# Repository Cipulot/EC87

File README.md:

# EC87

## **DEPRECATED**

This project has been deprecated in favor of the next TKL I'm working on.
It will not be updated nor maintained from now on, so do no base projects, them being PCB or cases, on it.
The project of reference for EC TKL will be named (provisional for now, in search of a better name still): ECip TKL
This new design will join the EC60 in the reference design family of PCBs that I'm working on. Think of these as the EC equivalent of the H87/88 and H60 for MX switches. An FRL will be developed too, to complete the general layouts. Both will feature the same key and cluster spacing as the H87/88 PCBs, so that future design of cases can have both MX and EC options without compromising compatibility or having to develop separate cases/parts of cases for it.

## Introduction

EC87 is an Electrostatic Capacitive (EC) TKL keyboard PCB.

This project is a continuation of my development of open source EC boards after publishing the [Corne EC Revival](https://github.com/Cipulot/CorneECRevival).

Below is the KLE of the supported layout:

Multi layout support is planned for Rev2.

## Technical information

- Layout size: tenkeykess (TKL)
- Compatible switches: EC switches (Topre and NIZ)
- Microcontroller: STM32F411
- Connector: detachable USB Type C
- Firmware compatibility: QMK (with VIA/VIAL support)
- Protection hardware:
  - Fused
  - ESD protection

## Renders and Prototypes

### EC87 PCB

#### Render

#### Prototype

### Plate

#### Render

#### Prototype

### Backplate

#### Render

#### Prototype

## Revisions and relative features

### Rev1

First revision of the board used for validation purposes of the circuit and QMK software.

Features include:

- Extension of the analog sensing circuit used in Corne EC Revival

- STM32F411 MCU for better performance, both cycle wise and in ADC performance compared to 32U4

- APC (Actuation Point Changer) with predefined actuation points and full scale analog switch control (full board / per key)

### Rev2

Rev 2 is already in the work and will have some radical changes, to allow better compatibility, layout options and performance improvements.

Features that will be included:

- Addition of multi-layout option (ANSI, ISO and different bottom rows)

- Rework of the analog circuit, basing it off a new "standard" model that is in development by [Gondolindrim](https://github.com/Gondolindrim) (absolute chad), myself and others. This so that we achieve a reliable enough design to enable more designers and more EC boards to get into the wild.

- Dedicated PCBs for specific MX boards already being run.

## WIP

Implementation of APC and initial calibration is in development. This features will allow to choose from a set op predetermined actuation points by simply cycling through them using a key combination. The initial calibration is to ensure that the overall baseline reading is equal across all the keys. Later, in Rev2, this will be used to adjust hardware gain through dedicated control circuit.

See commits in `Firmware` for details about the state of development.

## License

<br />This work is licensed under a <a rel="license" href="http://creativecommons.org/licenses/by-nc-sa/4.0/">Creative Commons Attribution-NonCommercial-ShareAlike 4.0 International License</a>.

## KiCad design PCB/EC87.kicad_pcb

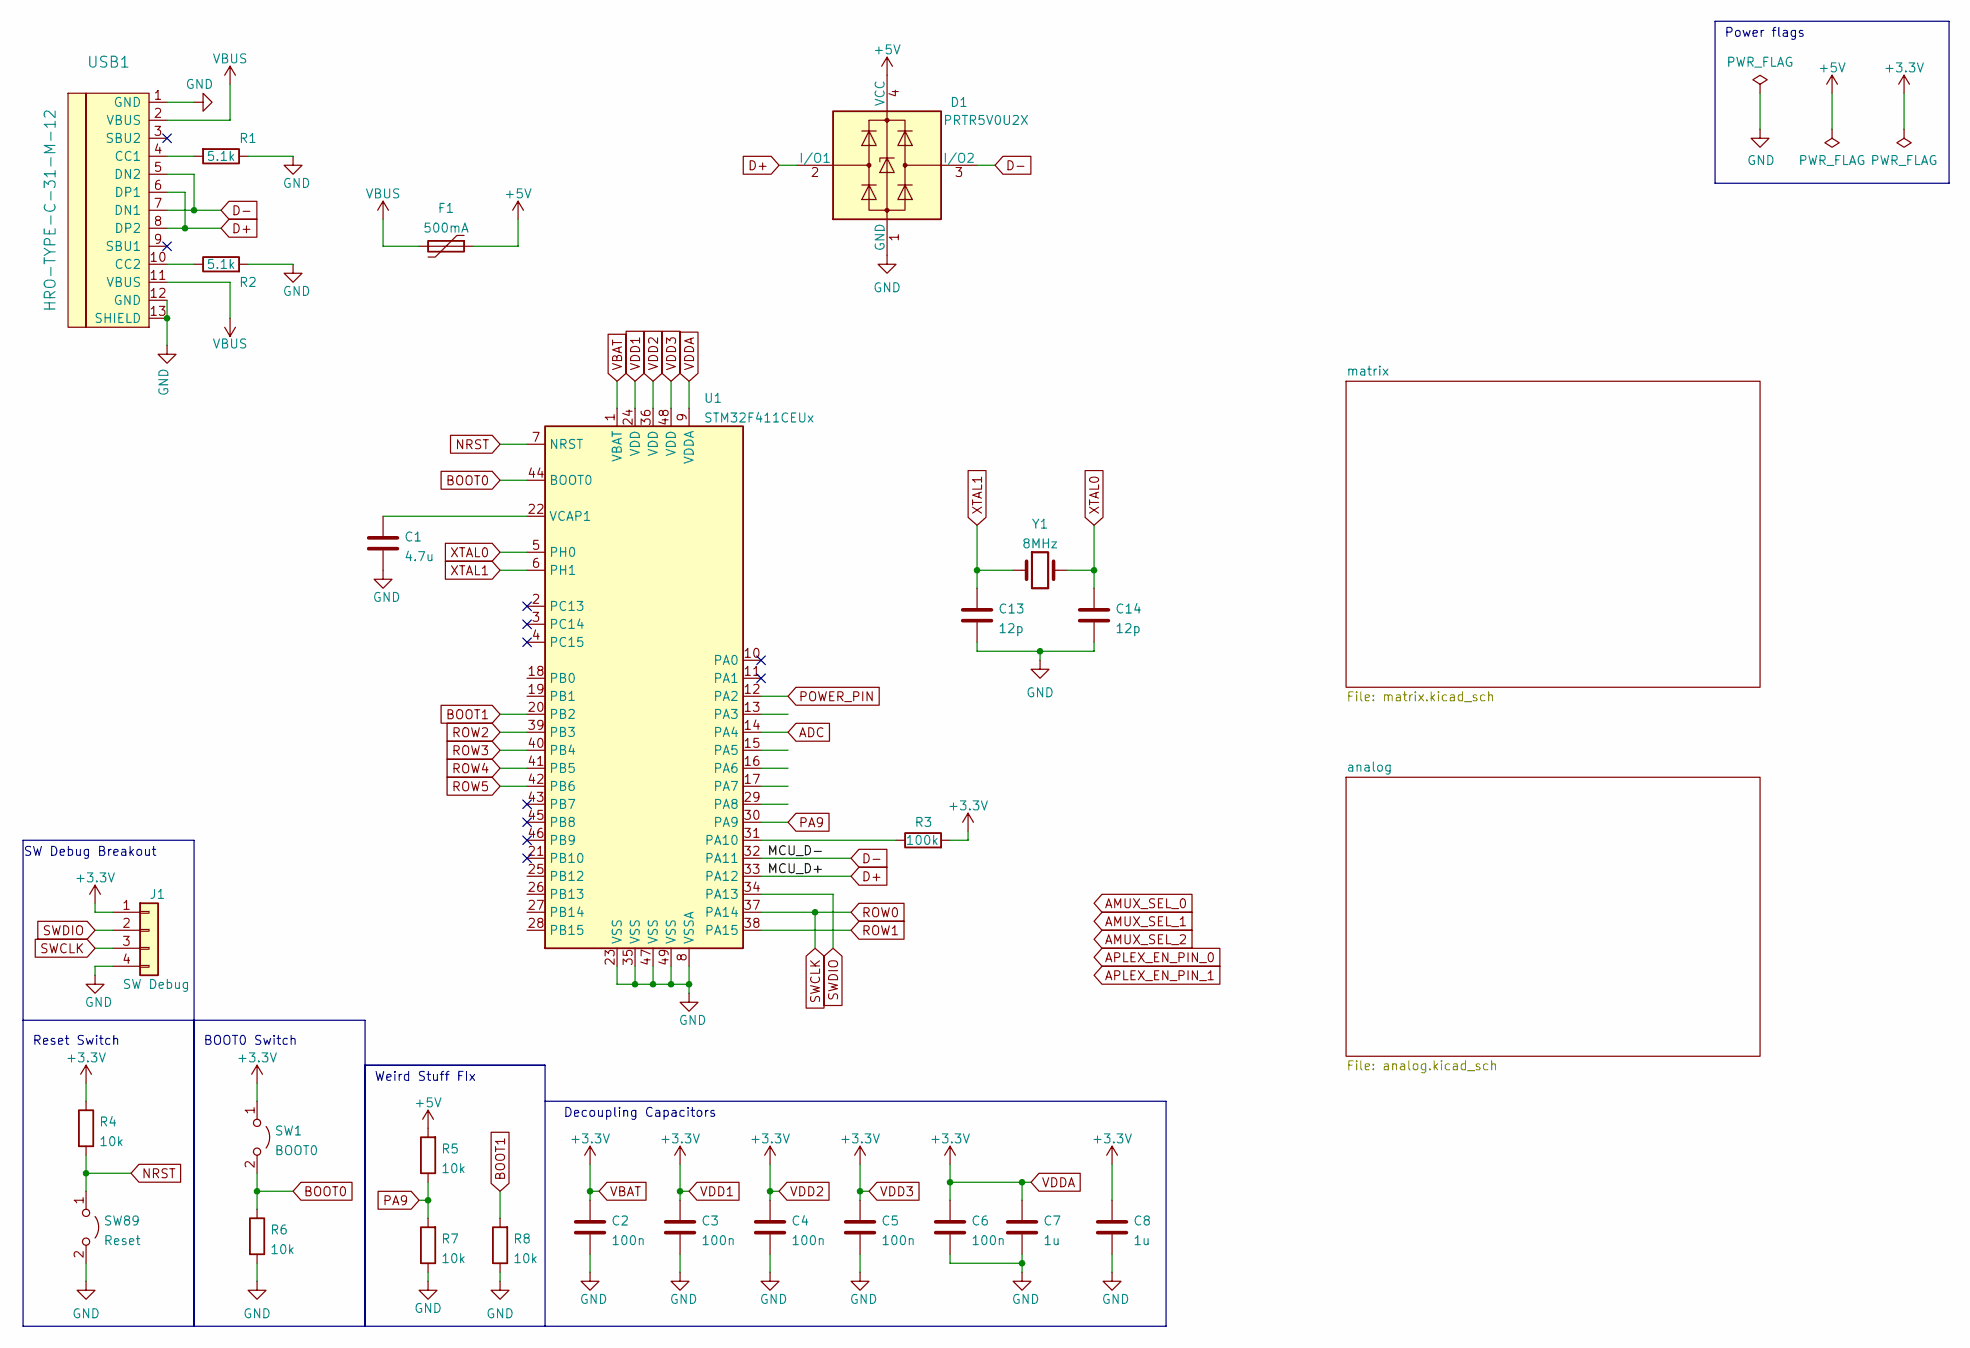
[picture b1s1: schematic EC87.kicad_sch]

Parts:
C1: 4.7u; C_0603_1608Metric
C2, C3, C4, C5, C6: 100n; C_0603_1608Metric
C7, C8: 1u; C_0603_1608Metric
C13, C14: 12p; C_0603_1608Metric
D1: PRTR5V0U2X; SOT-143
F1: 500mA; Fuse_1206_3216Metric
J1: SW Debug; PinHeader_1x04_P2.54mm_Vertical
R1, R2: 5.1k; R_0603_1608Metric
R3: 100k; R_0603_1608Metric
R4, R5, R6, R7, R8: 10k; R_0603_1608Metric
SW1: BOOT0; Jumper-UserFriendly
SW89: Reset; Jumper-UserFriendly
U1: STM32F411CEUx; QFN-48-1EP_7x7mm_P0.5mm_EP5.6x5.6mm
USB1: HRO-TYPE-C-31-M-12; HRO-TYPE-C-31-M-12-Assembly
Y1: 8MHz; Crystal_SMD_5032-2Pin_5.0x3.2mm

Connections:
+5V: D1.4 (VCC), F1.1, R5.2
ADC: U1.14 (PA4); also elsewhere on the board
BOOT0: R6.1, SW1.2 (B), U1.44 (BOOT0)
BOOT1: R8.2, U1.20 (PB2)
D+: D1.2 (I/O1), U1.33 (PA12), USB1.6 (DP1), USB1.8 (DP2)
D-: D1.3 (I/O2), U1.32 (PA11), USB1.5 (DN2), USB1.7 (DN1)
GND: C1.2, C2.2, C3.2, C4.2, C5.2, C6.2, C7.2, C8.2, C13.2, C14.2, D1.1 (GND), J1.4, R1.1, R2.2, R6.2, R7.1, R8.1, SW89.2 (B), U1.8 (VSSA), U1.23 (VSS), U1.35 (VSS), U1.47 (VSS), U1.49 (VSS), USB1.1 (GND), USB1.12 (GND), USB1.13 (SHIELD); also elsewhere on the board
NRST: R4.2, SW89.1 (A), U1.7 (NRST)
unnamed: C1.1, U1.22 (VCAP1)
unnamed: R1.2, USB1.4 (CC1)
unnamed: R2.1, USB1.10 (CC2)
unnamed: R3.1, U1.31 (PA10)
PA9: R5.1, R7.2, U1.30 (PA9)
POWER_PIN: U1.12 (PA2); also elsewhere on the board
ROW1: U1.38 (PA15); also elsewhere on the board
ROW2: U1.39 (PB3); also elsewhere on the board
ROW3: U1.40 (PB4); also elsewhere on the board
ROW4: U1.41 (PB5); also elsewhere on the board
ROW5: U1.42 (PB6); also elsewhere on the board
SWCLK: J1.3, U1.37 (PA14); also elsewhere on the board
SWDIO: J1.2, U1.34 (PA13)
VBAT: C2.1, C3.1, C4.1, C5.1, C6.1, C7.1, C8.1, J1.1, R3.2, R4.1, SW1.1 (A), U1.1 (VBAT), U1.9 (VDDA), U1.24 (VDD), U1.36 (VDD), U1.48 (VDD)
VBUS: F1.2, USB1.2 (VBUS), USB1.11 (VBUS)
XTAL0: C14.1, U1.5 (PH0), Y1.2
XTAL1: C13.1, U1.6 (PH1), Y1.1

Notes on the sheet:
BOOT0 Switch
Decoupling Capacitors
Weird Stuff FIx
Reset Switch
Power flags
SW Debug Breakout

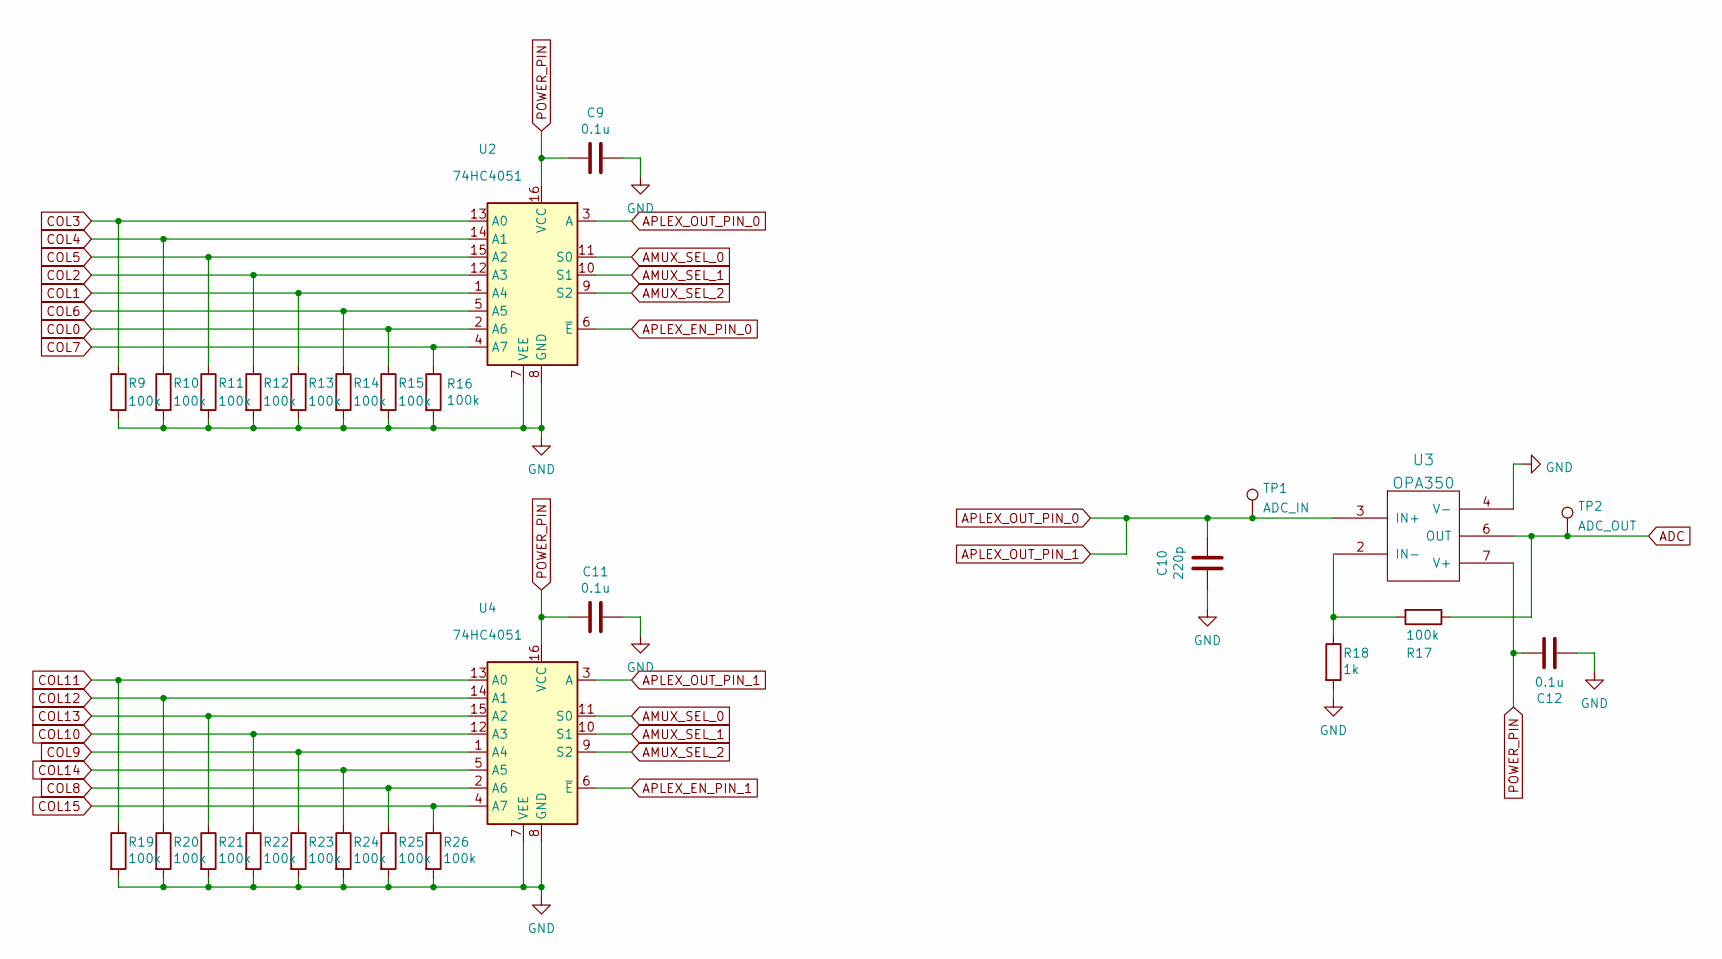
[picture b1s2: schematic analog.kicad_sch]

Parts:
C9, C11, C12: 0.1u; C_0603_1608Metric
C10: 220p; C_0603_1608Metric
R9, R10, R11, R12, R13, R14, R15, R16, R17, R19, R20, R21, R22, R23, R24, R25, R26: 100k; R_0603_1608Metric
R18: 1k; R_0603_1608Metric
TP1: ADC_IN; TestPoint_Pad_D1.0mm
TP2: ADC_OUT; TestPoint_Pad_D1.0mm
U2, U4: 74HC4051; TSSOP16
U3: OPA350; SOIC-8_3.9x4.9mm_P1.27mm

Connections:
ADC: R17.1, TP2.1, U3.6 (OUT); also elsewhere on the board
AMUX_SEL_0: U2.11 (S0), U4.11 (S0)
AMUX_SEL_1: U2.10 (S1), U4.10 (S1)
AMUX_SEL_2: U2.9 (S2), U4.9 (S2)
APLEX_EN_PIN_0: U2.6 (~E)
APLEX_EN_PIN_1: U4.6 (~E)
APLEX_OUT_PIN_0: C10.1, TP1.1, U2.3 (A), U3.3 (IN+), U4.3 (A)
COL0: R15.1, U2.2 (A6); also elsewhere on the board
COL1: R13.1, U2.1 (A4); also elsewhere on the board
COL2: R12.1, U2.12 (A3); also elsewhere on the board
COL3: R9.1, U2.13 (A0); also elsewhere on the board
COL4: R10.1, U2.14 (A1); also elsewhere on the board
COL5: R11.1, U2.15 (A2); also elsewhere on the board
COL6: R14.1, U2.5 (A5); also elsewhere on the board
COL7: R16.1, U2.4 (A7); also elsewhere on the board
COL8: R25.1, U4.2 (A6); also elsewhere on the board
COL9: R23.1, U4.1 (A4); also elsewhere on the board
COL10: R22.1, U4.12 (A3); also elsewhere on the board
COL11: R19.1, U4.13 (A0); also elsewhere on the board
COL12: R20.1, U4.14 (A1); also elsewhere on the board
COL13: R21.1, U4.15 (A2); also elsewhere on the board
COL14: R24.1, U4.5 (A5); also elsewhere on the board
COL15: R26.1, U4.4 (A7); also elsewhere on the board
GND: C9.1, C10.2, C11.1, C12.1, R9.2, R10.2, R11.2, R12.2, R13.2, R14.2, R15.2, R16.2, R18.2, R19.2, R20.2, R21.2, R22.2, R23.2, R24.2, R25.2, R26.2, U2.7 (VEE), U2.8 (GND), U3.4 (V-), U4.7 (VEE), U4.8 (GND); also elsewhere on the board
unnamed: R17.2, R18.1, U3.2 (IN-)
POWER_PIN: C9.2, C11.2, C12.2, U2.16 (VCC), U3.7 (V+), U4.16 (VCC); also elsewhere on the board

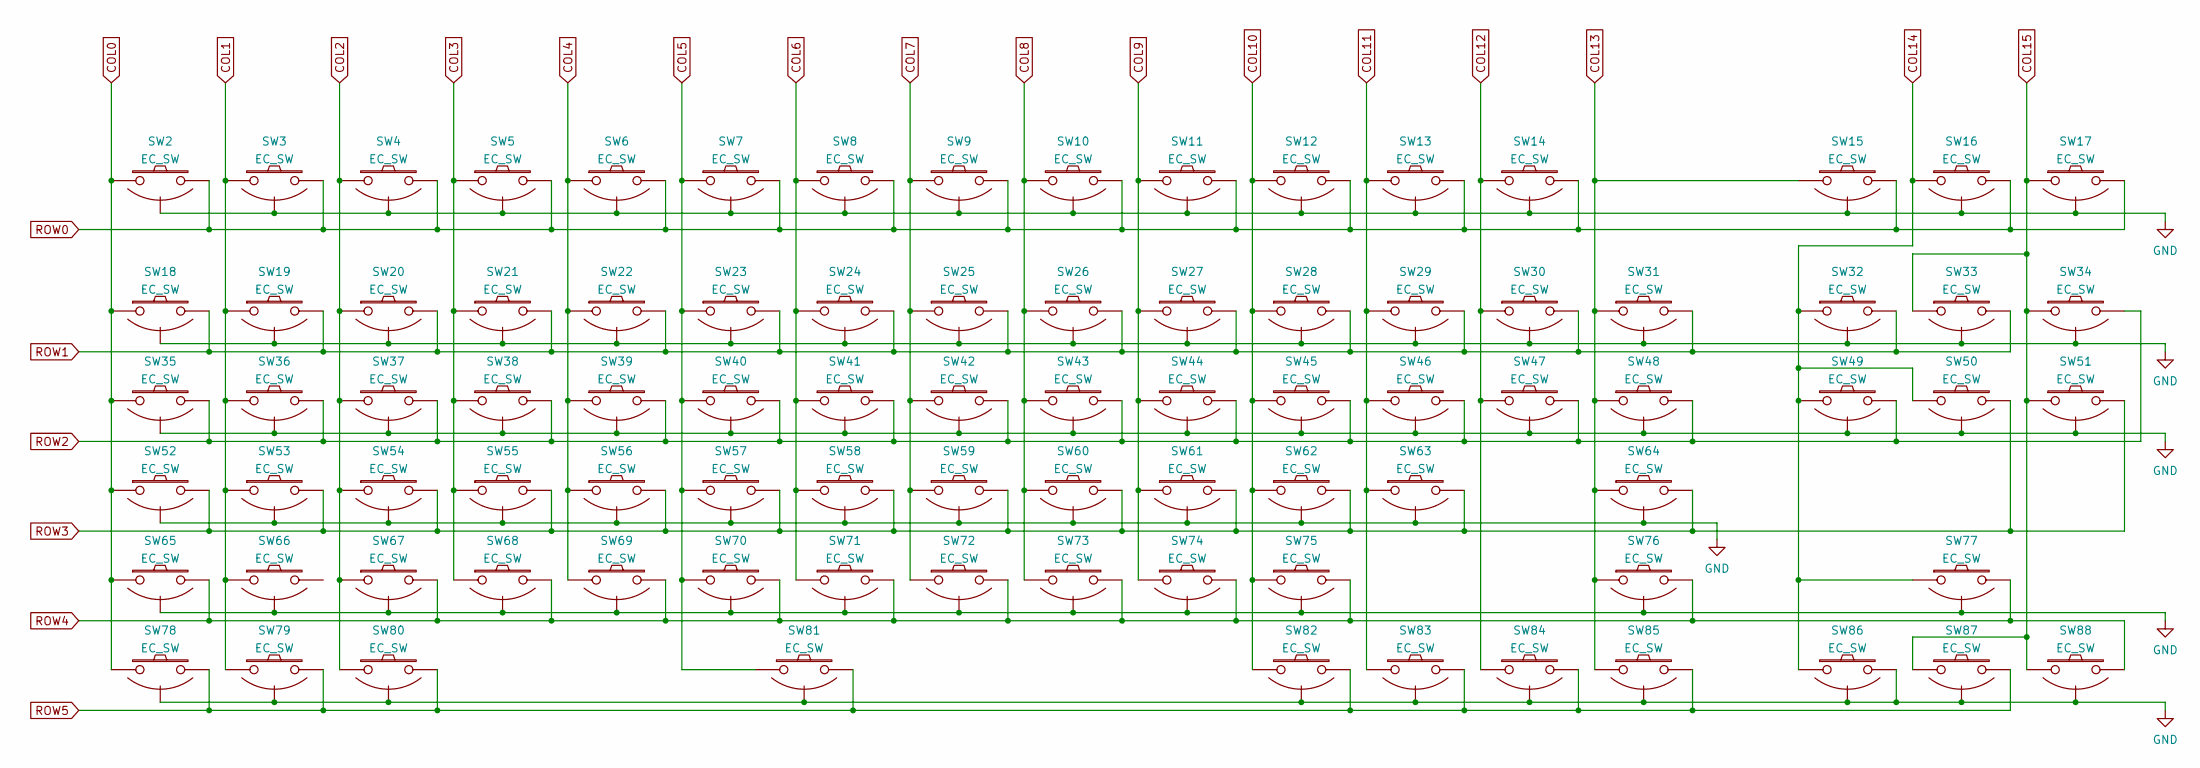
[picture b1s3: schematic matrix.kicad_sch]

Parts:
SW2, SW3, SW4, SW5, SW6, SW7, SW8, SW9, SW10, SW11, SW12, SW13, SW14, SW15, SW16, SW17, SW18, SW19, SW20, SW21, SW22, SW23, SW24, SW25, SW26, SW27, SW28, SW29, SW30, SW31, SW32, SW33, SW34, SW35, SW36, SW37, SW38, SW39, SW40, SW41, SW42, SW43, SW44, SW45, SW46, SW47, SW48, SW49, SW50, SW51, SW52, SW53, SW54, SW55, SW56, SW57, SW58, SW59, SW60, SW61, SW62, SW63, SW64, SW65, SW66, SW67, SW68, SW69, SW70, SW71, SW72, SW73, SW74, SW75, SW76, SW77, SW78, SW79, SW80, SW81, SW82, SW83, SW84, SW85, SW86, SW87, SW88: EC_SW; ecs_pad

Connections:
COL0: SW2.1, SW18.1, SW35.1, SW52.1, SW65.1, SW78.1; also elsewhere on the board
COL1: SW3.1, SW19.1, SW36.1, SW53.1, SW66.1, SW79.1; also elsewhere on the board
COL2: SW4.1, SW20.1, SW37.1, SW54.1, SW67.1, SW80.1; also elsewhere on the board
COL3: SW5.1, SW21.1, SW38.1, SW55.1, SW68.1; also elsewhere on the board
COL4: SW6.1, SW22.1, SW39.1, SW56.1, SW69.1; also elsewhere on the board
COL5: SW7.1, SW23.1, SW40.1, SW57.1, SW70.1, SW81.1; also elsewhere on the board
COL6: SW8.1, SW24.1, SW41.1, SW58.1, SW71.1; also elsewhere on the board
COL7: SW9.1, SW25.1, SW42.1, SW59.1, SW72.1; also elsewhere on the board
COL8: SW10.1, SW26.1, SW43.1, SW60.1, SW73.1; also elsewhere on the board
COL9: SW11.1, SW27.1, SW44.1, SW61.1, SW74.1; also elsewhere on the board
COL10: SW12.1, SW28.1, SW45.1, SW62.1, SW75.1, SW82.1; also elsewhere on the board
COL11: SW13.1, SW29.1, SW46.1, SW63.1, SW83.1; also elsewhere on the board
COL12: SW14.1, SW30.1, SW47.1, SW84.1; also elsewhere on the board
COL13: SW15.1, SW31.1, SW48.1, SW64.1, SW76.1, SW85.1; also elsewhere on the board
COL14: SW16.1, SW32.1, SW49.1, SW50.1, SW77.1, SW86.1; also elsewhere on the board
COL15: SW17.1, SW33.1, SW34.1, SW51.1, SW87.1, SW88.1; also elsewhere on the board
GND: SW2.3 (SG), SW3.3 (SG), SW4.3 (SG), SW5.3 (SG), SW6.3 (SG), SW7.3 (SG), SW8.3 (SG), SW9.3 (SG), SW10.3 (SG), SW11.3 (SG), SW12.3 (SG), SW13.3 (SG), SW14.3 (SG), SW15.3 (SG), SW16.3 (SG), SW17.3 (SG), SW18.3 (SG), SW19.3 (SG), SW20.3 (SG), SW21.3 (SG), SW22.3 (SG), SW23.3 (SG), SW24.3 (SG), SW25.3 (SG), SW26.3 (SG), SW27.3 (SG), SW28.3 (SG), SW29.3 (SG), SW30.3 (SG), SW31.3 (SG), SW32.3 (SG), SW33.3 (SG), SW34.3 (SG), SW35.3 (SG), SW36.3 (SG), SW37.3 (SG), SW38.3 (SG), SW39.3 (SG), SW40.3 (SG), SW41.3 (SG), SW42.3 (SG), SW43.3 (SG), SW44.3 (SG), SW45.3 (SG), SW46.3 (SG), SW47.3 (SG), SW48.3 (SG), SW49.3 (SG), SW50.3 (SG), SW51.3 (SG), SW52.3 (SG), SW53.3 (SG), SW54.3 (SG), SW55.3 (SG), SW56.3 (SG), SW57.3 (SG), SW58.3 (SG), SW59.3 (SG), SW60.3 (SG), SW61.3 (SG), SW62.3 (SG), SW63.3 (SG), SW64.3 (SG), SW65.3 (SG), SW66.3 (SG), SW67.3 (SG), SW68.3 (SG), SW69.3 (SG), SW70.3 (SG), SW71.3 (SG), SW72.3 (SG), SW73.3 (SG), SW74.3 (SG), SW75.3 (SG), SW76.3 (SG), SW77.3 (SG), SW78.3 (SG), SW79.3 (SG), SW80.3 (SG), SW81.3 (SG), SW82.3 (SG), SW83.3 (SG), SW84.3 (SG), SW85.3 (SG), SW86.2, SW86.3 (SG), SW87.3 (SG), SW88.3 (SG); also elsewhere on the board
ROW1: SW18.2, SW19.2, SW20.2, SW21.2, SW22.2, SW23.2, SW24.2, SW25.2, SW26.2, SW27.2, SW28.2, SW29.2, SW30.2, SW31.2, SW32.2, SW33.2; also elsewhere on the board
ROW2: SW34.2, SW35.2, SW36.2, SW37.2, SW38.2, SW39.2, SW40.2, SW41.2, SW42.2, SW43.2, SW44.2, SW45.2, SW46.2, SW47.2, SW48.2, SW49.2; also elsewhere on the board
ROW3: SW50.2, SW51.2, SW52.2, SW53.2, SW54.2, SW55.2, SW56.2, SW57.2, SW58.2, SW59.2, SW60.2, SW61.2, SW62.2, SW63.2, SW64.2; also elsewhere on the board
ROW4: SW65.2, SW67.2, SW68.2, SW69.2, SW70.2, SW71.2, SW72.2, SW73.2, SW74.2, SW75.2, SW76.2, SW77.2, SW88.2; also elsewhere on the board
ROW5: SW78.2, SW79.2, SW80.2, SW81.2, SW82.2, SW83.2, SW84.2, SW85.2, SW87.2; also elsewhere on the board
SWCLK: SW2.2, SW3.2, SW4.2, SW5.2, SW6.2, SW7.2, SW8.2, SW9.2, SW10.2, SW11.2, SW12.2, SW13.2, SW14.2, SW15.2, SW16.2, SW17.2; also elsewhere on the board

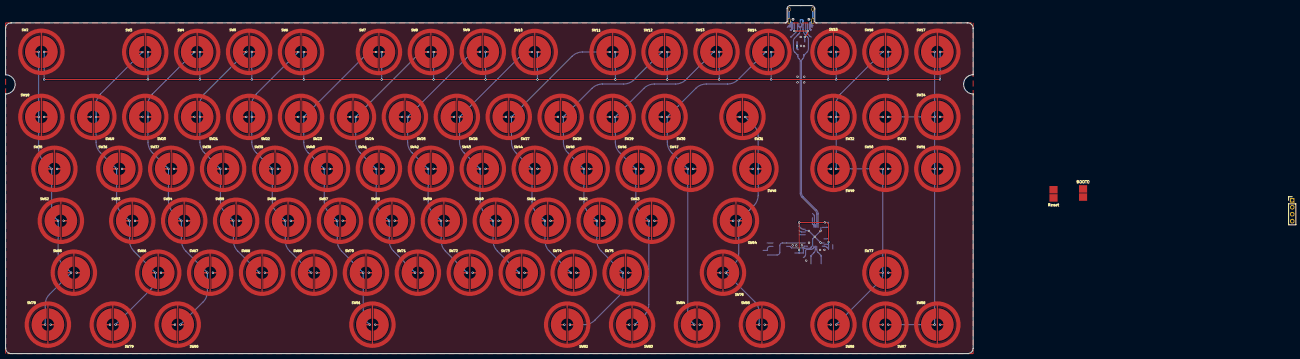
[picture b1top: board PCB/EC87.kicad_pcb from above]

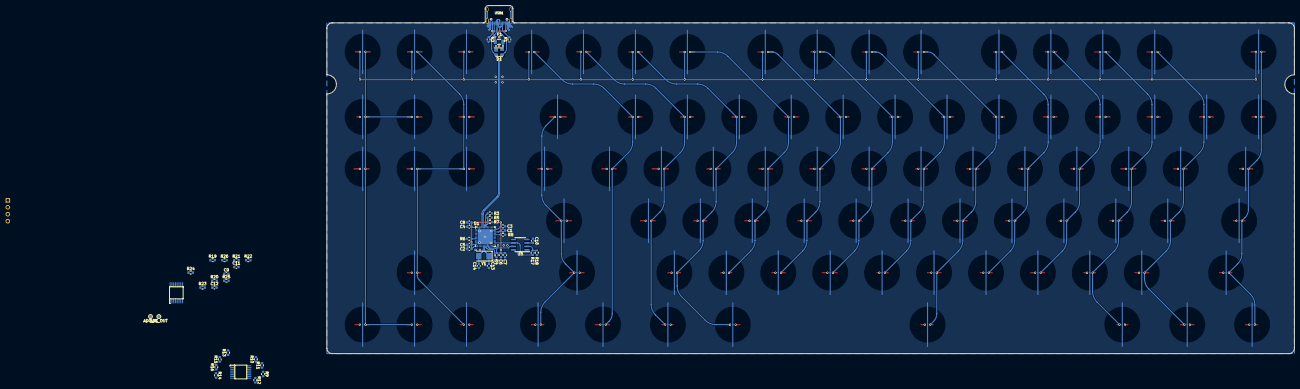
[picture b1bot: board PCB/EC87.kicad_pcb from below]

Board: 2 copper layers, 354.0 x 127.3 mm, 140 parts (50 on the bottom side), 46 nets.

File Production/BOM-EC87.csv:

Comment,Designator,Footprint,LCSC
OPA350,U3,SOIC-8_3.9x4.9mm_P1.27mm,C13388
100k,R24,R_0603_1608Metric,C25803
100n,C4,C_0603_1608Metric,C14663
100k,R20,R_0603_1608Metric,C25803
100k,R3,R_0603_1608Metric,C25803
100k,R13,R_0603_1608Metric,C25803
PRTR5V0U2X,D1,SOT-143,C2827688
100k,R12,R_0603_1608Metric,C25803
100k,R11,R_0603_1608Metric,C25803
10k,R5,R_0603_1608Metric,C25804
0.1u,C9,C_0603_1608Metric,C14663
100k,R19,R_0603_1608Metric,C25803
74HC4051,U4,TSSOP16,C5645
STM32F411CEUx,U1,QFN-48-1EP_7x7mm_P0.5mm_EP5.6x5.6mm,C60420
100k,R26,R_0603_1608Metric,C25803
100k,R23,R_0603_1608Metric,C25803
100k,R21,R_0603_1608Metric,C25803
10k,R8,R_0603_1608Metric,C25804
74HC4051,U2,TSSOP16,C5645
0.1u,C12,C_0603_1608Metric,C14663
100k,R25,R_0603_1608Metric,C25803
220p,C10,C_0603_1608Metric,C302060
10k,R7,R_0603_1608Metric,C25804
0.1u,C11,C_0603_1608Metric,C14663
100k,R10,R_0603_1608Metric,C25803
100n,C6,C_0603_1608Metric,C14663
10k,R4,R_0603_1608Metric,C25804
100n,C3,C_0603_1608Metric,C14663
100k,R17,R_0603_1608Metric,C25803
500mA,F1,Fuse_1206_3216Metric,C70076
100k,R9,R_0603_1608Metric,C25803
HRO-TYPE-C-31-M-12,USB1,HRO-TYPE-C-31-M-12-Assembly,C165948
100k,R22,R_0603_1608Metric,C25803
100k,R16,R_0603_1608Metric,C25803
10k,R6,R_0603_1608Metric,C25804
100n,C5,C_0603_1608Metric,C14663
5.1k,R1,R_0603_1608Metric,C23186
100k,R15,R_0603_1608Metric,C25803
1k,R18,R_0603_1608Metric,C21190
100k,R14,R_0603_1608Metric,C25803
5.1k,R2,R_0603_1608Metric,C23186
4.7u,C1,C_0603_1608Metric,C19666
100n,C2,C_0603_1608Metric,C14663
1u,C8,C_0603_1608Metric,C15849
1u,C7,C_0603_1608Metric,C15849

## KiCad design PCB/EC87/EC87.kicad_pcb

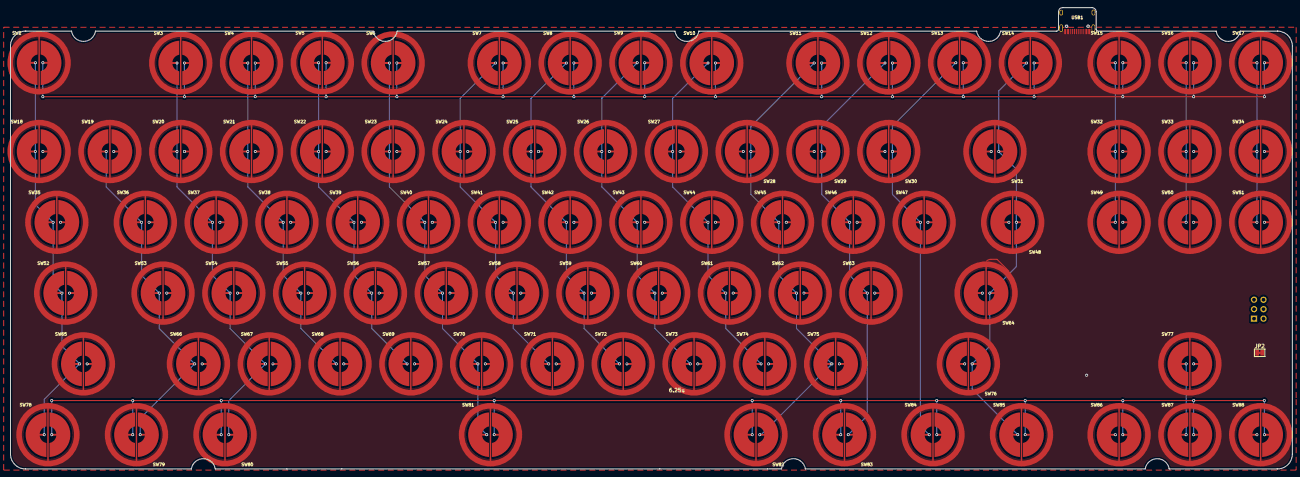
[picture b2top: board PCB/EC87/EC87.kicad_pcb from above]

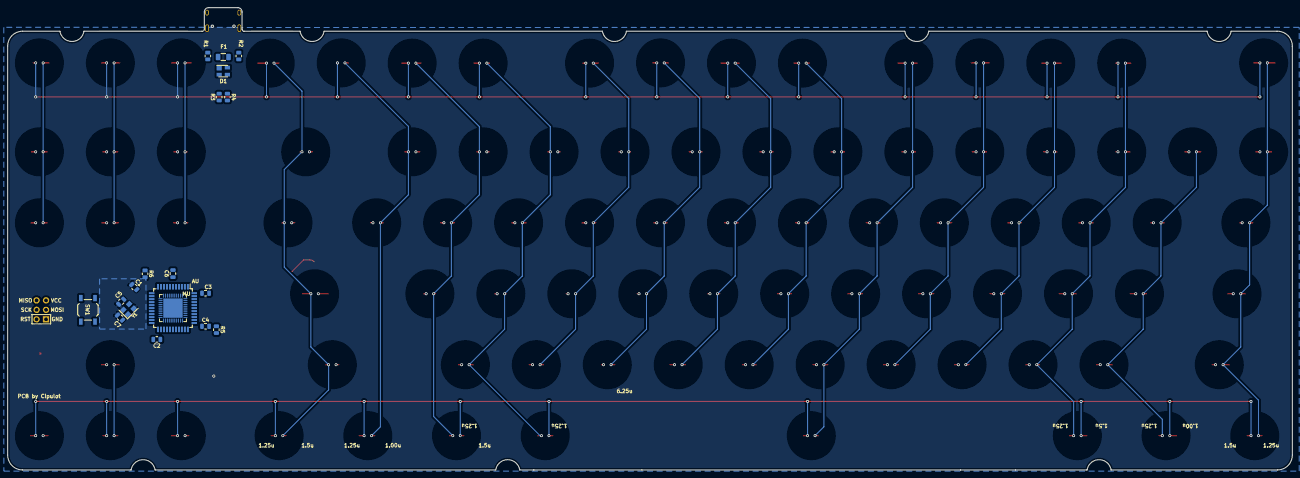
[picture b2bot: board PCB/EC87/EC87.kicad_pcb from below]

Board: 2 copper layers, 344.0 x 123.8 mm, 109 parts (20 on the bottom side), 46 nets.

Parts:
AU: ATmega32U4-A; TQFP-44_10x10mm_P0.8mm
C1, C2, C3: 0.1u; C_0805_2012Metric
C4: 10u; C_0805_2012Metric
C5, C7: 22p; C_0805_2012Metric
C6: 1u; C_0805_2012Metric
D1: PRTR5V0U2X; SOT-143
F1: 500mA; Fuse_1206_3216Metric
J1: AVR-ISP-6-Connector; Reset_Pretty
JP2: Jumper_NC_Small; SolderJumper-2_P1.3mm_Bridged_Pad1.0x1.5mm
MU: QFN-44-1EP_7x7mm_P0.5mm_EP5.2x5.2mm
R1, R2: 5.1k; R_0805_2012Metric
R3, R4: 22; R_0805_2012Metric
R5, R6: 10k; R_0805_2012Metric
SW1: SW_Push; SW_SPST_TL3342
SW2, SW3, SW4, SW5, SW6, SW7, SW8, SW9, SW10, SW11, SW12, SW13, SW14, SW15, SW16, SW17, SW18, SW19, SW20, SW21, SW22, SW23, SW24, SW25, SW26, SW27, SW28, SW29, SW30, SW31, SW32, SW33, SW34, SW35, SW36, SW37, SW38, SW39, SW40, SW41, SW42, SW43, SW44, SW45, SW46, SW47, SW48, SW49, SW50, SW51, SW52, SW53, SW54, SW55, SW56, SW57, SW58, SW59, SW60, SW61, SW62, SW63, SW64, SW65, SW66, SW67, SW68, SW69, SW70, SW71, SW72, SW73, SW74, SW75, SW76, SW77, SW78, SW79, SW80, SW81, SW82, SW83, SW84, SW85, SW86, SW87, SW88: EC_SW; ecs_pad
USB1: HRO-TYPE-C-31-M-12; HRO-TYPE-C-31-M-12-Assembly
Y1: 16MHz; Crystal_SMD_3225-4pin_3.2x2.5mm

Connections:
/MCU_D+: AU.4 (D+), MU.4, R3.2
/MCU_D-: AU.3 (D-), MU.3, R4.2
COL0: AU.41 (PF0), MU.41, SW2.1, SW18.1, SW35.1, SW52.1, SW65.1, SW78.1
COL1: AU.40 (PF1), MU.40, SW19.1, SW36.1, SW53.1, SW66.1, SW79.1
COL2: AU.39 (PF4), MU.39, SW3.1, SW20.1, SW37.1, SW54.1, SW67.1, SW80.1
COL3: AU.38 (PF5), MU.38, SW4.1, SW21.1, SW38.1, SW55.1, SW68.1
COL4: AU.37 (PF6), MU.37, SW5.1, SW22.1, SW39.1, SW56.1, SW69.1
COL5: AU.36 (PF7), MU.36, SW6.1, SW23.1, SW40.1, SW57.1, SW70.1, SW81.1
COL6: AU.32 (PC7), MU.32, SW7.1, SW24.1, SW41.1, SW58.1, SW71.1
COL7: AU.31 (PC6), MU.31, SW8.1, SW25.1, SW42.1, SW59.1, SW72.1
COL8: AU.20 (PD2), MU.20, SW9.1, SW26.1, SW43.1, SW60.1, SW73.1
COL9: SW10.1, SW27.1, SW44.1, SW61.1, SW74.1
COL10: SW11.1, SW28.1, SW45.1, SW62.1, SW75.1, SW82.1
COL11: SW12.1, SW29.1, SW46.1, SW63.1, SW83.1
COL12: SW13.1, SW30.1, SW47.1, SW84.1
COL13: SW14.1, SW31.1, SW48.1, SW64.1, SW76.1, SW85.1
COL14: SW15.1, SW32.1, SW49.1, SW86.1
COL15: SW16.1, SW33.1, SW50.1, SW77.1, SW87.1
COL16: SW17.1, SW34.1, SW51.1, SW88.1
Caps_LED: AU.22 (PD5), MU.22
D+: D1.2 (I/O1), R3.1, USB1.6 (DP1), USB1.8 (DP2)
D-: D1.3 (I/O2), R4.1, USB1.5 (DN2), USB1.7 (DN1)
GND: AU.5 (UGND), AU.15 (GND), AU.23 (GND), AU.35 (GND), AU.43 (GND), C1.2, C2.2, C3.2, C4.2, C5.1, C6.2, C7.1, D1.1 (GND), J1.6 (GND), JP2.2, MU.5, MU.15, MU.23, MU.35, MU.43, MU.45, R1.1, R2.2, R5.2, SW1.1, USB1.1 (GND), USB1.12 (GND), USB1.13 (SHIELD), Y1.2, Y1.4
GNDA: JP2.1, SW2.3 (SG), SW3.3 (SG), SW4.3 (SG), SW5.3 (SG), SW6.3 (SG), SW7.3 (SG), SW8.3 (SG), SW9.3 (SG), SW10.3 (SG), SW11.3 (SG), SW12.3 (SG), SW13.3 (SG), SW14.3 (SG), SW15.3 (SG), SW16.3 (SG), SW17.3 (SG), SW18.3 (SG), SW19.3 (SG), SW20.3 (SG), SW21.3 (SG), SW22.3 (SG), SW23.3 (SG), SW24.3 (SG), SW25.3 (SG), SW26.3 (SG), SW27.3 (SG), SW28.3 (SG), SW29.3 (SG), SW30.3 (SG), SW31.3 (SG), SW32.3 (SG), SW33.3 (SG), SW34.3 (SG), SW35.3 (SG), SW36.3 (SG), SW37.3 (SG), SW38.3 (SG), SW39.3 (SG), SW40.3 (SG), SW41.3 (SG), SW42.3 (SG), SW43.3 (SG), SW44.3 (SG), SW45.3 (SG), SW46.3 (SG), SW47.3 (SG), SW48.3 (SG), SW49.3 (SG), SW50.3 (SG), SW51.3 (SG), SW52.3 (SG), SW53.3 (SG), SW54.3 (SG), SW55.3 (SG), SW56.3 (SG), SW57.3 (SG), SW58.3 (SG), SW59.3 (SG), SW60.3 (SG), SW61.3 (SG), SW62.3 (SG), SW63.3 (SG), SW64.3 (SG), SW65.3 (SG), SW66.3 (SG), SW67.3 (SG), SW68.3 (SG), SW69.3 (SG), SW70.3 (SG), SW71.3 (SG), SW72.3 (SG), SW73.3 (SG), SW74.3 (SG), SW75.3 (SG), SW76.3 (SG), SW77.3 (SG), SW78.3 (SG), SW79.3 (SG), SW80.3 (SG), SW81.3 (SG), SW82.3 (SG), SW83.3 (SG), SW84.3 (SG), SW85.3 (SG), SW86.3 (SG), SW87.3 (SG), SW88.3 (SG)
MISO: AU.11 (PB3), J1.1 (MISO), MU.11, SW52.2, SW53.2, SW54.2, SW55.2, SW56.2, SW57.2, SW58.2, SW59.2, SW60.2, SW61.2, SW62.2, SW63.2, SW64.2
MOSI: AU.10 (PB2), J1.4 (MOSI), MU.10, SW35.2, SW36.2, SW37.2, SW38.2, SW39.2, SW40.2, SW41.2, SW42.2, SW43.2, SW44.2, SW45.2, SW46.2, SW47.2, SW48.2, SW49.2, SW50.2, SW51.2
unnamed: AU.6 (UCAP), C6.1, MU.6
unnamed: R1.2, USB1.4 (CC1)
unnamed: R2.1, USB1.10 (CC2)
unnamed: AU.33 (~HWB/PE2), MU.33, R5.1
ROW0: AU.8 (PB0), MU.8, SW2.2, SW3.2, SW4.2, SW5.2, SW6.2, SW7.2, SW8.2, SW9.2, SW10.2, SW11.2, SW12.2, SW13.2, SW14.2, SW15.2, SW16.2, SW17.2
ROW1: AU.9 (PB1), J1.3 (SCK), MU.9, SW18.2, SW19.2, SW20.2, SW21.2, SW22.2, SW23.2, SW24.2, SW25.2, SW26.2, SW27.2, SW28.2, SW29.2, SW30.2, SW31.2, SW32.2, SW33.2, SW34.2
ROW4: AU.18 (PD0), MU.18, SW65.2, SW67.2, SW68.2, SW69.2, SW70.2, SW71.2, SW72.2, SW73.2, SW74.2, SW75.2, SW76.2, SW77.2
ROW5: AU.19 (PD1), MU.19, SW78.2, SW79.2, SW80.2, SW81.2, SW82.2, SW83.2, SW84.2, SW85.2, SW86.2, SW87.2, SW88.2
ROW6: AU.29 (PB5), MU.29
ROW7: AU.30 (PB6), MU.30
ROW8: AU.27 (PD7), MU.27
ROW9: AU.28 (PB4), MU.28
ROW10: AU.26 (PD6), MU.26
ROW11: AU.25 (PD4), MU.25
RST: AU.13 (~RESET), J1.5 (~RST), MU.13, R6.2, SW1.2
Scroll_LED: AU.1 (PE6), MU.1
VBUS: F1.2, USB1.2 (VBUS), USB1.11 (VBUS)
VCC: AU.2 (UVCC), AU.7 (VBUS), AU.14 (VCC), AU.24 (AVCC), AU.34 (VCC), AU.44 (AVCC), C1.1, C2.1, C3.1, C4.1, D1.4 (VCC), F1.1, J1.2 (VCC), MU.2, MU.7, MU.14, MU.24, MU.34, MU.44, R6.1
XTAL1: AU.17 (XTAL1), C7.2, MU.17, Y1.1
XTAL2: AU.16 (XTAL2), C5.2, MU.16, Y1.3

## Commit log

2022-03-08 Update repo structure
2022-03-08 Revert "Update repo structure"
    This reverts commit af9b34d953d0568c00315420b9b34d4b01439f36.
2022-03-22 Update cipulot_kicad_parts
2022-03-24 Firmware dump and PCB update
2022-03-26 Update final schematic and PCB
    PCB and schematic are finalized, now proceeding to addition of GND vias to shield from parasitic capacitance.
2022-03-27 Update of via placement
2022-03-28 Update of PCB for production of first proto
2022-03-28 Update of plate and production folder fix
2022-03-29 Added stabs cutouts
2022-03-29 Update for production and added backplate
2022-03-29 Update firmware
2022-03-29 Fix of firmware
2022-03-29 Update of backplate
2022-03-29 VIA firmware
2022-03-29 Update backplate silkscreen
2022-03-29 Code update
2022-03-30 Update of schematic infos and backplate
2022-03-30 Create LICENSE
2022-04-05 Clean-up of docs and update firmware
2022-04-11 Applied updated EC pad footprint
2022-04-12 Update plate
2022-04-12 Update plate 2u holes
2022-04-15 Update of folder structure
2022-04-16 Update to fix mounting point and add vias
2022-04-16 Upload of images
2022-04-16 Update to remove logo
2022-04-16 Plate model update
2022-04-19 VIAL support
2022-04-19 Upload images of PCB proto
2022-04-19 Image rename
2022-04-19 Addition of Proto pictures
2022-04-20 Update firmware to include debug options
2022-04-21 Updated firmware
    Instead of fixed HIGH and LOW threshold for the whole keyboard you can now define different actuation levels for each key in the matrix. Change these values in the 2 matrix defined in `matrix.c`.
2022-04-26 Update of README to include extra proto pics
2022-04-27 Updated KLE image
    Fix spacing and key assignment.
2022-04-27 Updated KLE image
2022-04-27 Update KLE image final
2022-05-12 Added Caps Lock LED on SWDIO pin and fixed calibration
2022-06-04 Typo fix
2022-07-26 Align to new USB defs file in info.json
2022-08-09 FIX Production files
    Fix to the production files that caused one of the 2 EC pads to be merged with the ground plane.
2024-03-03 Updated the License for the project and relative details.
